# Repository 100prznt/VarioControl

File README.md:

# VarioControl
IoT pump control for Vario pumps with 0 - 10 V interface.

------------

## Current build state

Unassembled PCB in matching Spelsberg enclosure. (2021/06/06)

## Hardware Features

+ 0 - 10 V interface for speed control of a Vario pump
+ WiFi interface
+ 1-wire interface for two DS18B20 temperature sensors
+ 0 - 10 V input for a pressure sensor (alt. also 0 - 5 V or 4 - 20 mA possible)
+ Switch input for operating mode preselection (AUTO - OFF - MANUAL)
+ 5 LEDs for status visualization
+ Wide range power supply (12 - 36 V)

## PCB

## AquaTechnix AquaVarioPlus

### Setup

The external control of the AquaVarioPlus can be activated in the setup menu of the pump. This is described in detail in the manual (of the BADU Eco Soft, which has the same control) on page 9 an 10. The "Steuerart" (control type) 0 - 10 V, code 3 is required.

* [Manual BADU EcoSoft](docu/BA_BADU_EcoSoft.pdf)

### Connector

Control board of the AquaVarioPlus pump from AquaTechnix.

The CN4 (pin 2) connector is provided for controlling the pump via the 0 - 10 V interface. See also [Manual BADU EcoSoft](docu/BA_BADU_EcoSoft.pdf) on page 7.

#### Pinning

| pin# | function        | specification                    | in use with VarioControl |    
|-----:|:----------------|:---------------------------------|:------------------------:|
| 1    | n/a             |                                  | :heavy_multiplication_x: |
| 2    | rpm value (U)   | 0 - 10 V                         | :heavy_check_mark:       |
| 3    | PWM             | unknow specs?                    | :heavy_multiplication_x: |
| 4    | rpm value (I)   | 4 - 20 mA                        | :heavy_multiplication_x: |
| 5    | GND             |                                  | :heavy_check_mark:       |

The control via the "PWM" input I have experimented with a frequency generator with various settings, unfortunately without success. I believe that the software implementation and a corresponding preselection of the control type is missing here.

#### Type
The plug used is probably a clone of the JST XH connector series, which has been modified to add an external locking mechanism. Plugs of this type are tricky to find, but an original XH plug from JST fits and holds very well.

| Manufacturer                     | SKU       |
|:---------------------------------|:----------|
| JST (JAPAN SOLDERLESS TERMINALS) | __XHP-5__ |

Suitable contacts are listed in the data sheet on page 2.

* [Datasheet JST XH Connector](docu/jst-xh.pdf)

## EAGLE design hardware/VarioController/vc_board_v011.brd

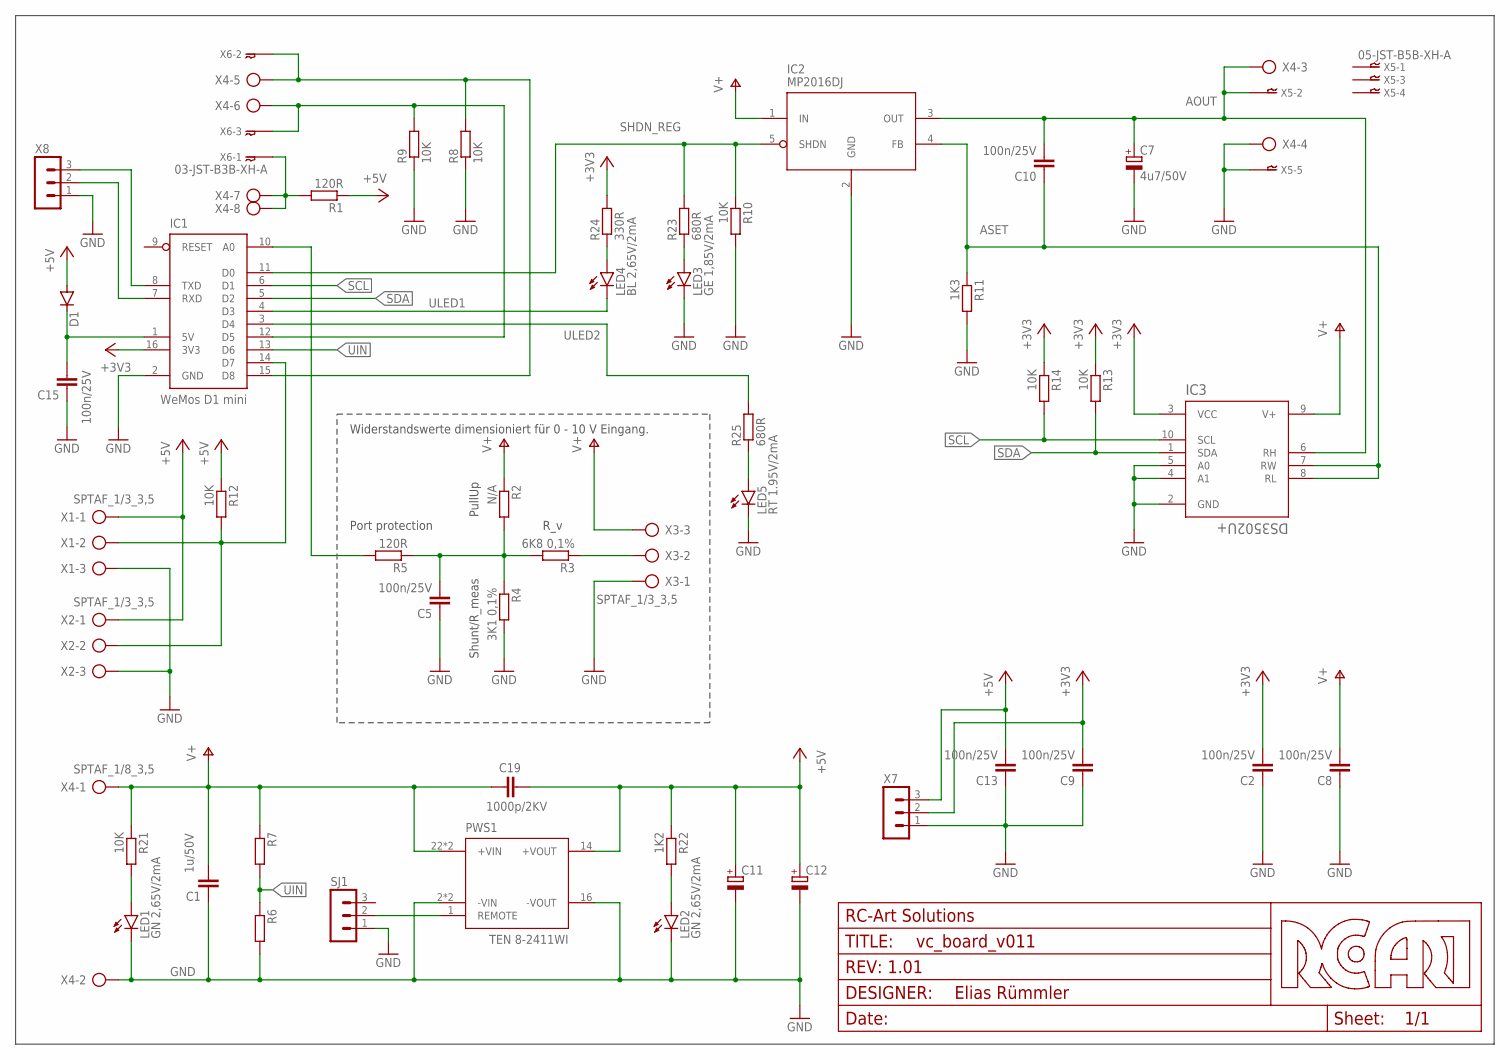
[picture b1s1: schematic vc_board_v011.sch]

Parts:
C1: 1u/50V; C1210K
C2, C5, C8, C9, C10, C13, C15: 100n/25V; C0805
C7: 4u7/50V; D/7343-31W
C11, C12: CPOL-EUD/7343-31W; D/7343-31W
C19: 1000p/2KV; C1206K
D1: DIODE-SMB; SMB
FRAME1: MF_FRAMEDEFAULT; MF_FRAME_DEFAULT
IC1: WeMos D1 mini; D1_MINI
IC2: MP2016DJ; TSOT23-5
IC3: DS3502U+; 21-0061L_MXM
LED1, LED2: GN 2,65V/2mA; CHIPLED_0805; FARNELL_SKU 2846598
LED3: GE 1,85V/2mA; CHIPLED_0805; FARNELL_SKU 2846596
LED4: BL 2,65V/2mA; CHIPLED_0805; FARNELL_SKU 2846594
LED5: RT 1.95V/2mA; CHIPLED_0805; FARNELL_SKU 2099241
PWS1: TEN 8-2411WI; TEN8
R1, R5: 120R; R0805
R2: N/A; R0805
R3: 6K8 0,1%; R0805
R4: 3K1 0,1%; R0805
R6, R7: R-EU_R0805; R0805
R8, R9, R10, R12, R13, R14, R21: 10K; R0805
R11: 1K3; R0805
R22: 1K2; R0805
R23, R25: 680R; R0805
R24: 330R; R0805
SJ1: MA03-1
X1, X2, X3: SPTAF_1/3_3,5
X4: SPTAF_1/8_3,5
X5: 05-JST-B5B-XH-A; B5B-XH
X6: 03-JST-B3B-XH-A; B3B-XH
X7, X8: MA03-1

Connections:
+3V3: C2.2, C9.2, IC1.16 (3V3), IC3.3 (VCC), R13.1, R14.1, R24.2, X7.2
+5V: C11.+, C12.+, C13.2, C19.2, D1.A, PWS1.14 (+VOUT), R1.1, R12.1, R22.1, X1.1, X1.1A, X2.1, X2.1A, X7.3
AOUT: C7.+, C10.2, IC2.3 (OUT), IC3.6 (RH), X4.3, X4.3A, X5.P$2
ASET: C10.1, IC2.4 (FB), IC3.7 (RW), IC3.8 (RL), R11.1
GND: C1.1, C2.1, C5.1, C7.-, C8.1, C9.1, C11.-, C12.-, C13.1, C15.1, IC1.2 (GND), IC2.2 (GND), IC3.2 (GND), IC3.4 (A1), IC3.5 (A0), LED1.C, LED2.C, LED3.C, LED5.C, PWS1.2 (-VIN), PWS1.3 (-VIN), PWS1.16 (-VOUT), R4.2, R6.2, R8.1, R9.1, R10.2, R11.2, SJ1.1, X1.3, X1.3A, X2.3, X2.3A, X3.1, X3.1A, X4.2, X4.2A, X4.4, X4.4A, X5.P$5, X7.1, X8.1
unnamed: C5.2, R2.2, R3.2, R4.1, R5.1
unnamed: IC1.12 (D5), R9.2, X4.6, X4.6A, X6.P$3
unnamed: IC1.15 (D8), R8.2, X4.5, X4.5A, X6.P$2
unnamed: R1.2, X4.7, X4.7A, X4.8, X4.8A, X6.P$1
unnamed: R3.1, X3.2, X3.2A
unnamed: C15.2, D1.C, IC1.1 (5V)
unnamed: PWS1.1 (REMOTE), SJ1.2
unnamed: LED3.A, R23.1
unnamed: LED1.A, R21.2
unnamed: LED2.A, R22.2
unnamed: IC1.14 (D7), R12.2, X1.2, X1.2A, X2.2, X2.2A
unnamed: IC1.8 (TXD), X8.3
unnamed: IC1.7 (RXD), X8.2
unnamed: LED4.A, R24.1
unnamed: LED5.A, R25.1
unnamed: IC1.10 (A0), R5.2
SCL: IC1.6 (D1), IC3.10 (SCL), R14.2
SDA: IC1.5 (D2), IC3.1 (SDA), R13.2
SHDN_REG: IC1.11 (D0), IC2.5 (SHDN), R10.1, R23.2
UIN: IC1.13 (D6), R6.1, R7.2
ULED1: IC1.4 (D3), LED4.C
ULED2: IC1.3 (D4), R25.2
V+: C1.2, C8.2, C19.1, IC2.1 (IN), IC3.9 (V+), PWS1.22 (+VIN), PWS1.23 (+VIN), R2.1, R7.1, R21.1, X3.3, X3.3A, X4.1, X4.1A

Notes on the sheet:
PullUp
Shunt/R_meas
R_v
Port protection
Widerstandswerte dimensioniert für 0 - 10 V Eingang.

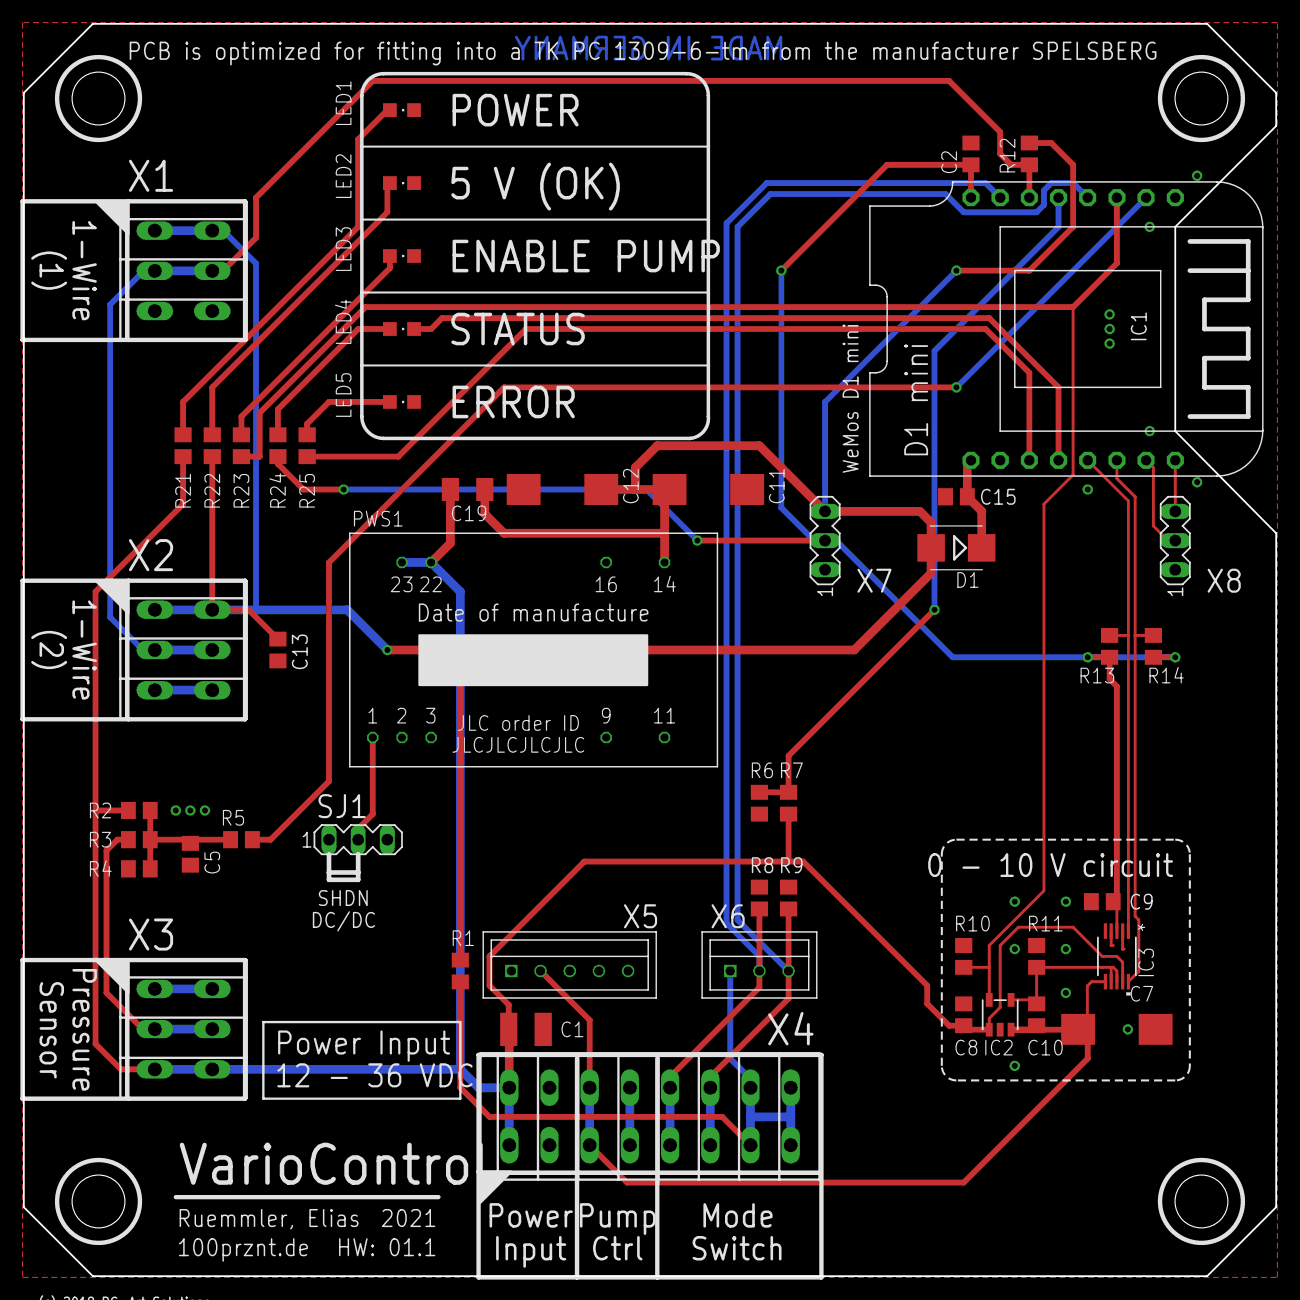
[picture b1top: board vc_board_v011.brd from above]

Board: 2 copper layers, 109.0 x 109.0 mm, 51 parts (0 on the bottom side), 28 nets.

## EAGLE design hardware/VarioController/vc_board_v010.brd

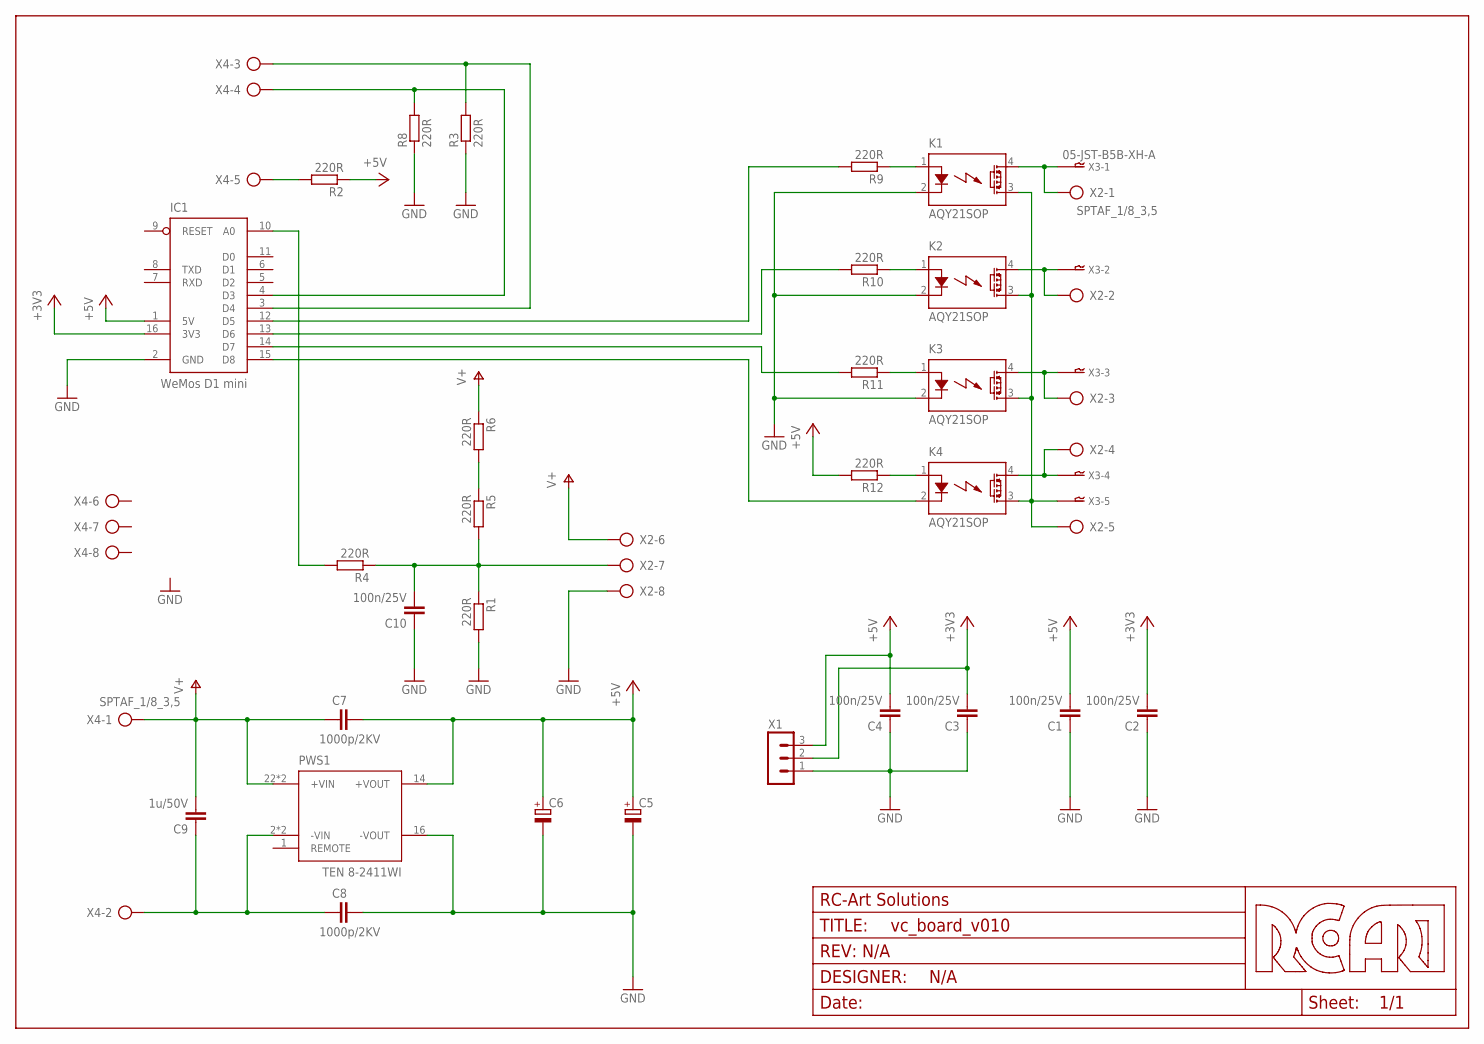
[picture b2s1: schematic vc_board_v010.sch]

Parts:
C1, C2, C3, C4, C10: 100n/25V; C0805
C5, C6: CPOL-EUCT7343; CT7343
C7, C8: 1000p/2KV; C1206K
C9: 1u/50V; C1210K
FRAME1: MF_FRAMEDEFAULT; MF_FRAME_DEFAULT
IC1: WeMos D1 mini; D1_MINI
K1, K2, K3, K4: AQY21SOP; SOP04
PWS1: TEN 8-2411WI; TEN8
R1, R2, R3, R4, R5, R6, R8, R9, R10, R11, R12: 220R; R0805
X1: MA03-1
X2, X4: SPTAF_1/8_3,5
X3: 05-JST-B5B-XH-A; B5B-XH

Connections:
+3V3: C2.2, C3.2, IC1.16 (3V3), X1.2
+5V: C1.2, C4.2, C5.+, C6.+, C7.2, IC1.1 (5V), PWS1.14 (+VOUT), R2.1, R12.2, X1.3
GND: C1.1, C2.1, C3.1, C4.1, C5.-, C6.-, C8.2, C10.1, IC1.2 (GND), K1.2 (K), K2.2 (K), K3.2 (K), PWS1.16 (-VOUT), R1.2, R3.1, R8.1, X1.1, X2.8, X2.8A
unnamed: C10.2, R1.1, R4.1, R5.2, X2.7, X2.7A
unnamed: IC1.4 (D3), R8.2, X4.4, X4.4A
unnamed: IC1.3 (D4), R3.2, X4.3, X4.3A
unnamed: C8.1, C9.1, PWS1.2 (-VIN), PWS1.3 (-VIN), X4.2, X4.2A
unnamed: R2.2, X4.5, X4.5A
unnamed: K1.3 (DS2), K2.3 (DS2), K3.3 (DS2), K4.3 (DS2), X2.5, X2.5A, X3.P$5
unnamed: K4.4 (DS1), X2.4, X2.4A, X3.P$4
unnamed: K3.4 (DS1), X2.3, X2.3A, X3.P$3
unnamed: K2.4 (DS1), X2.2, X2.2A, X3.P$2
unnamed: K1.4 (DS1), X2.1, X2.1A, X3.P$1
unnamed: K4.1 (A), R12.1
unnamed: R5.1, R6.2
unnamed: K3.1 (A), R11.1
unnamed: K2.1 (A), R10.1
unnamed: K1.1 (A), R9.1
unnamed: IC1.15 (D8), K4.2 (K)
unnamed: IC1.14 (D7), R11.2
unnamed: IC1.13 (D6), R10.2
unnamed: IC1.12 (D5), R9.2
unnamed: IC1.10 (A0), R4.2
V+: C7.1, C9.2, PWS1.22 (+VIN), PWS1.23 (+VIN), R6.1, X2.6, X2.6A, X4.1, X4.1A

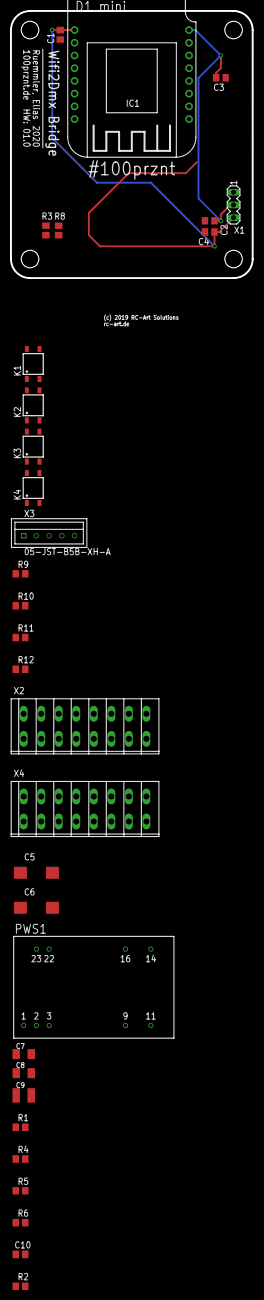
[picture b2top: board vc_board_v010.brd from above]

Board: 2 copper layers, 48.3 x 53.3 mm, 32 parts (0 on the bottom side), 24 nets.

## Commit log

2021-04-16 Add docu
2021-04-16 v011
2021-04-23 Add layout
2021-04-26 Update PCB
2021-04-26 update layout
2021-04-27 PCB ORDER!
2021-04-27 Add green renderings
2021-04-27 rename
2021-04-28 Update values
2021-05-20 Update docu
2021-05-20 upd docu
2023-12-16 add image

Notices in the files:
parts and their libraries:
rca-frames: (c) 2019 RC-Art Solutions
